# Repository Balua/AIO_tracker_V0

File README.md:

### AIO_Tracker_V1.0 - Beware, we are still testing this board...

#### Corrections and alterations to this board can be found in the AIO_tracker_V1.0 repository.

#### Features:

#####Microprocessor
- ATMEGA 328p smd package

#####Power
- Step up Boost Converters from 2 AA Batteries to 3.3V and 5V

#####Communication
- Radiometrix HX1 - VHF Narrow Band FM High Power (300mW) Transmitter with SMA Antenna
- RFM22B ISM Transceiver Module with SMA Antenna

#####GPS
- Ublox Max 6 GPS with Sarantel antenna

#####Sensors
- One wire temperature sensor - DS18B20
- Battery Voltage
- Pressure Sensor - HSCSANN015PA2A3 

#####Storage
- MicroSD Socket

#####Programming
- AVR SPI Programming pins available

#####External pins
- I2c Pins with pull-up for expansion available
- 4 ADC Pins available

#####Other
- On Board AA battery holder
- 5V boost converter with enable controllable
- UBlox GPS Power ON Controllable
- On board LED
- 5V/3.3V smd jumpers available for Atmega 328p, i2c and SPI Programming pins.

#### Erros detected and Corrections that need to be done

- Replace tx pin of HX1 from PD4 to PD3 in atmega 328 and 5V enable from PD3 to PD4.
- SDN pin of the RFM22b is low activated, therefore needs to be connected to GND instead of 3.3V.

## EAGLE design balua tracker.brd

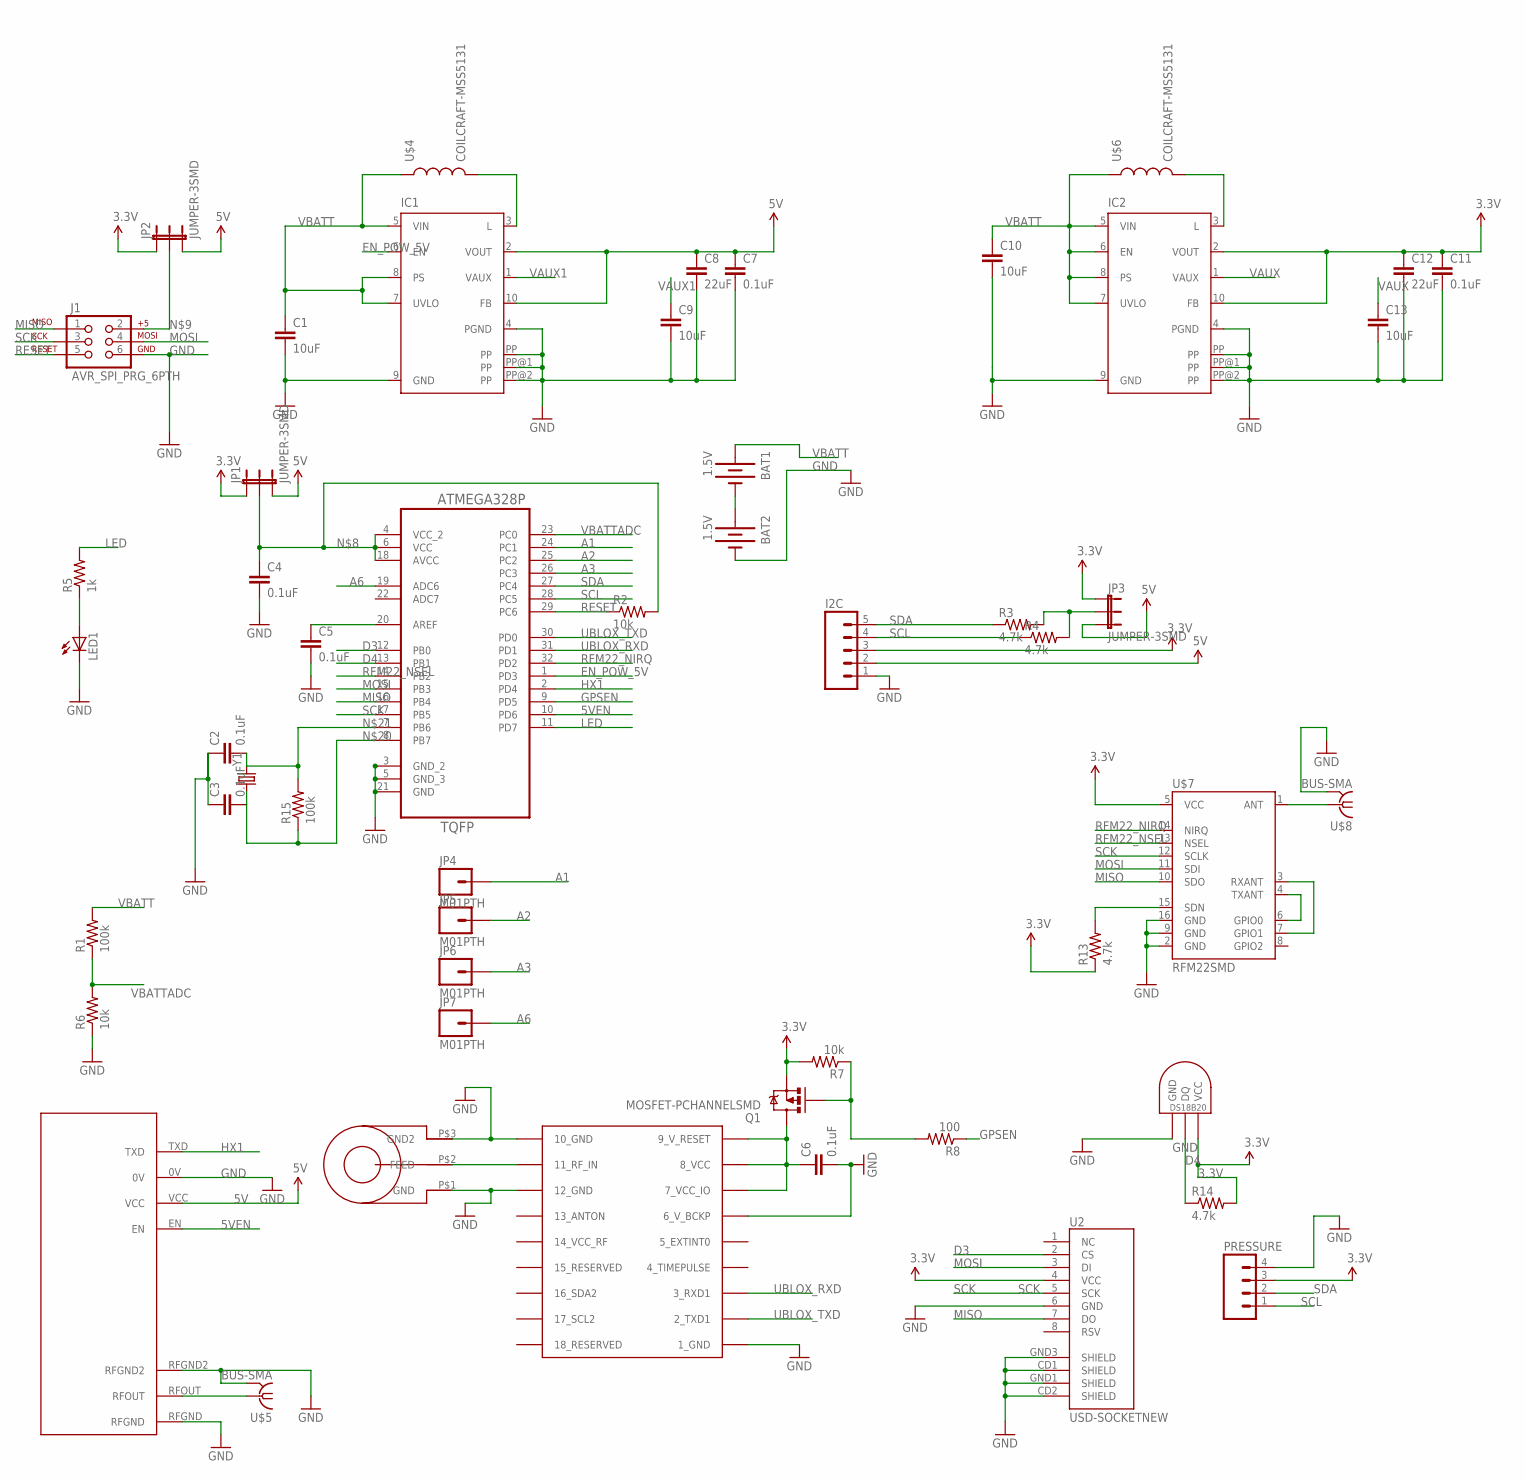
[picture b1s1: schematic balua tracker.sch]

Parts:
BAT1, BAT2: 1.5V; BATTERY-AA-KIT
C1, C9, C10, C13: 10uF; 0603-CAP
C2, C3, C4, C5, C6, C7, C11: 0.1uF; 0603-CAP
C8, C12: 22uF; 0603-CAP
I2C: M05PTH; 1X05
IC1, IC2: TPS61201; S-PDSO-N10
J1: AVR_SPI_PRG_6PTH; 2X3
JP1, JP2, JP3: JUMPER-3SMD; SJ_3
JP4, JP5, JP6, JP7: M01PTH; 1X01
LED1: LED0603; LED-0603
PRESSURE: M04PTH; 1X04
Q1: MOSFET-PCHANNELSMD; SOT23-3
R1, R15: 100k; 0603-RES
R2, R6, R7: 10k; 0603-RES
R3, R4, R13, R14: 4.7k; 0603-RES
R5: 1k; 0603-RES
R8: 100; 0603-RES
U1: ATMEGA328P-AU; QFP80P900X900X120-32N
U2: USD-SOCKETNEW; MICRO-SD-SOCKET-PP
U$1: UBLOX_MAX-6
U$2: SARANTEL-SL1250
U$3: RADIOMETRIX-HX1
U$4, U$6: COILCRAFT-MSS5131; COILCRAFT_MSS5131
U$5, U$8: BUS-SMA
U$7: RFM22SMD; RFM22-XXX-S2
U$9: DS1820TO92; DS1820
Y1: CRYSTAL10.5X4.8; CRYSTAL-SMD-10.5X4.8-2PIN

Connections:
3.3V: C11.1, C12.1, I2C.3, IC2.2 (VOUT), IC2.10 (FB), JP1.1, JP2.1, JP3.1, PRESSURE.3, Q1.2 (S), R7.2, R13.1, R14.2, U2.4 (VCC), U$7.5 (VCC), U$9.VDD (VCC)
5V: C7.1, C8.1, I2C.2, IC1.2 (VOUT), IC1.10 (FB), JP1.3, JP2.3, JP3.3, U$3.VCC
5VEN: U1.10 (PD6), U$3.EN
A1: JP4.1, U1.24 (PC1)
A2: JP5.1, U1.25 (PC2)
A3: JP6.1, U1.26 (PC3)
A6: JP7.1, U1.19 (ADC6)
D3: U1.12 (PB0), U2.2 (CS)
D4: R14.1, U1.13 (PB1), U$9.DQ
EN_POW_5V: IC1.6 (EN), U1.1 (PD3)
GND: BAT2.GND@1 (-), C1.2, C2.1, C3.1, C4.2, C5.2, C6.2, C7.2, C8.2, C9.2, C10.2, C11.2, C12.2, C13.2, I2C.1, IC1.4 (PGND), IC1.9 (GND), IC1.PP, IC1.PP@1 (PP), IC1.PP@2 (PP), IC2.4 (PGND), IC2.9 (GND), IC2.PP, IC2.PP@1 (PP), IC2.PP@2 (PP), J1.6, LED1.C, PRESSURE.4, R6.1, U1.3 (GND_2), U1.5 (GND_3), U1.21 (GND), U2.6 (GND), U2.CD1 (SHIELD), U2.CD2 (SHIELD), U2.GND1 (SHIELD), U2.GND3 (SHIELD), U$1.1_GND, U$1.6_V_BCKP, U$1.10_GND, U$1.12_GND, U$2.P$1 (GND), U$2.P$3 (GND2), U$3.0V, U$3.RFGND, U$3.RFGND2, U$5.2 (GND), U$5.3 (GND), U$5.4 (GND), U$5.5 (GND), U$7.2 (GND), U$7.9 (GND), U$7.16 (GND), U$8.2 (GND), U$8.3 (GND), U$8.4 (GND), U$8.5 (GND), U$9.GND
GPSEN: R8.1, U1.9 (PD5)
HX1: U1.2 (PD4), U$3.TXD
LED: R5.2, U1.11 (PD7)
MISO: J1.1, U1.16 (PB4), U2.7 (DO), U$7.10 (SDO)
MOSI: J1.4, U1.15 (PB3), U2.3 (DI), U$7.11 (SDI)
unnamed: LED1.A, R5.1
unnamed: Q1.1 (G), R7.1, R8.2
unnamed: U$1.11_RF_IN, U$2.P$2 (FEED)
unnamed: C5.1, U1.20 (AREF)
unnamed: U$3.RFOUT, U$5.1
unnamed: C6.1, Q1.3 (D), U$1.7_VCC_IO, U$1.8_VCC, U$1.9_V_RESET
unnamed: IC1.3 (L), U$4.P$1 (2)
unnamed: C4.1, JP1.2, R2.2, U1.4 (VCC_2), U1.6 (VCC), U1.18 (AVCC)
unnamed: J1.2, JP2.2
unnamed: BAT1.GND@1 (-), BAT2.PWR@1 (+)
unnamed: U$7.1 (ANT), U$8.1
unnamed: JP3.2, R3.2, R4.2
unnamed: IC2.3 (L), U$6.P$1 (2)
unnamed: C3.2, R15.1, U1.8 (PB7), Y1.P$1 (1)
unnamed: C2.2, R15.2, U1.7 (PB6), Y1.P$2 (2)
unnamed: R13.2, U$7.15 (SDN)
unnamed: U$7.3 (RXANT), U$7.7 (GPIO1)
unnamed: U$7.4 (TXANT), U$7.6 (GPIO0)
RESET: J1.5, R2.1, U1.29 (PC6)
RFM22_NIRQ: U1.32 (PD2), U$7.14 (NIRQ)
RFM22_NSEL: U1.14 (PB2), U$7.13 (NSEL)
SCK: J1.3, U1.17 (PB5), U2.5 (SCK), U$7.12 (SCLK)
SCL: I2C.4, PRESSURE.1, R4.1, U1.28 (PC5)
SDA: I2C.5, PRESSURE.2, R3.1, U1.27 (PC4)
UBLOX_RXD: U1.31 (PD1), U$1.3_RXD1
UBLOX_TXD: U1.30 (PD0), U$1.2_TXD1
VAUX: C13.1, IC2.1 (VAUX)
VAUX1: C9.1, IC1.1 (VAUX)
VBATT: BAT1.PWR@1 (+), C1.1, C10.1, IC1.5 (VIN), IC1.7 (UVLO), IC1.8 (PS), IC2.5 (VIN), IC2.6 (EN), IC2.7 (UVLO), IC2.8 (PS), R1.2, U$4.P$2 (1), U$6.P$2 (1)
VBATTADC: R1.1, R6.2, U1.23 (PC0)

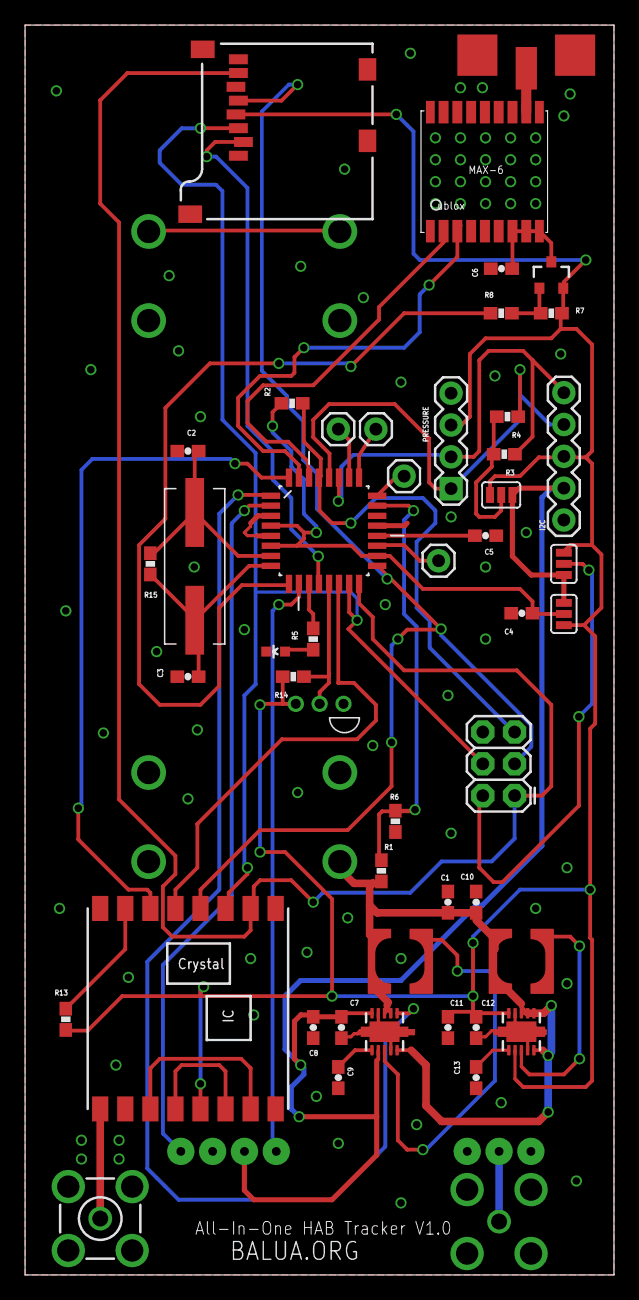
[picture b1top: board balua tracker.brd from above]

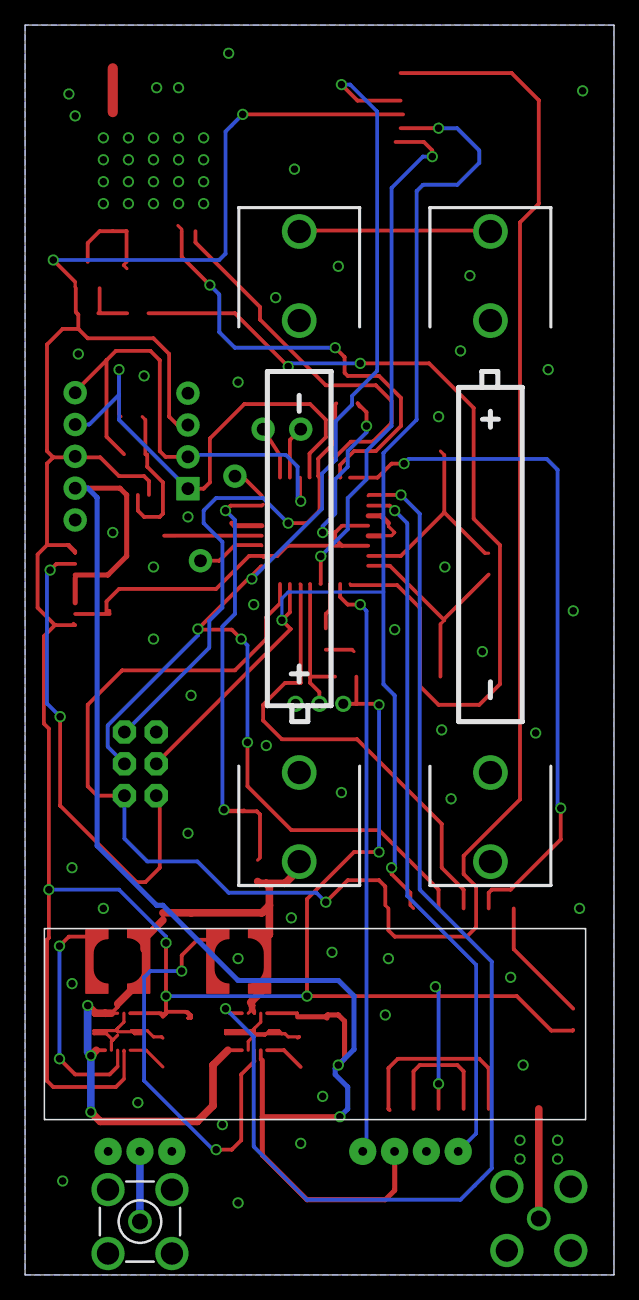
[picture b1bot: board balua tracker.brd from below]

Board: 2 copper layers, 47.0 x 99.8 mm, 52 parts (4 on the bottom side), 46 nets.

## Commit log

2014-06-30 Balua Tracker
    Balua tracker sent to print in hackvana.
    Beware, we are still testing this board
2014-07-21 Updated Read Me with the erros and corrections
    Updated Read me with the erros and corrections made to the pcb after the
    first flight test.
2014-08-10 Added pcb and stencil photos

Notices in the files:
parts and their libraries:
SparkFun-Passives: Licensing: CC v3.0 Share-Alike You are welcome to use this library for commercial purposes.
